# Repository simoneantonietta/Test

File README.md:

# Test
Test repository

The repository contains PCB and uC project files

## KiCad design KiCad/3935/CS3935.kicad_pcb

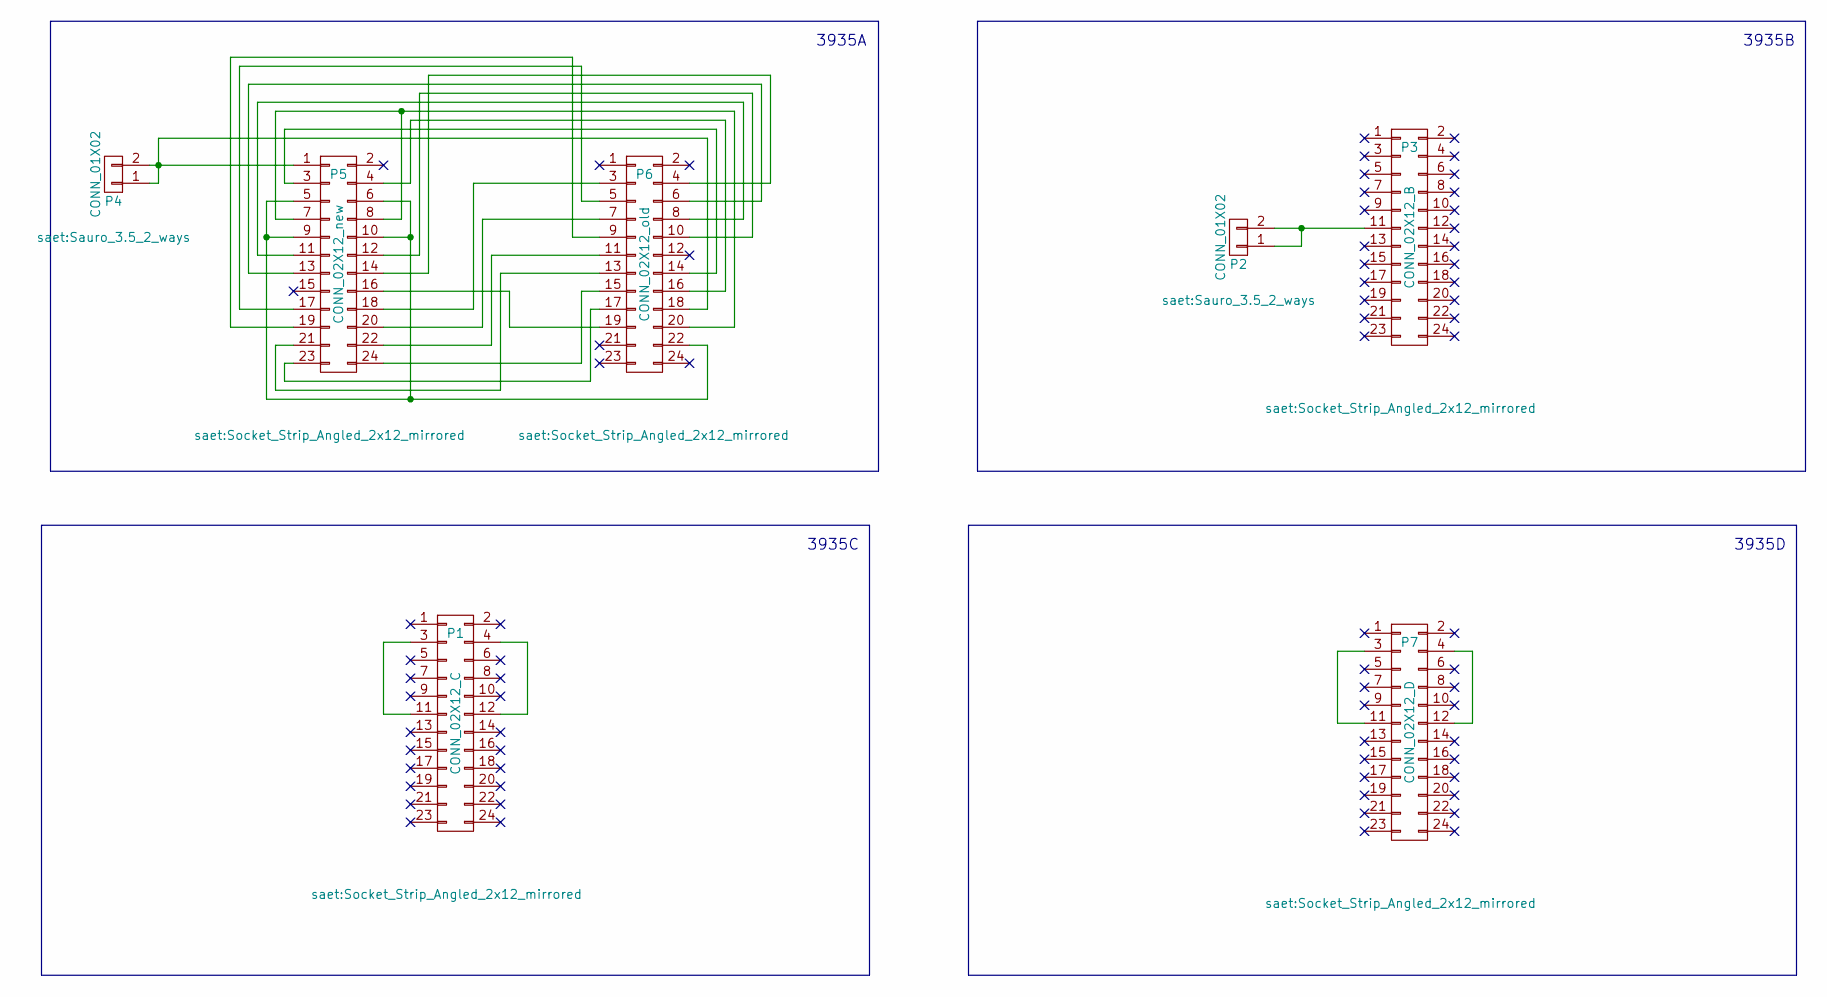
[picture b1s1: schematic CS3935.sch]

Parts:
P1: CONN_02X12_C; Socket_Strip_Angled_2x12_mirrored
P2, P4: CONN_01X02; Sauro_3.5_2_ways
P3: CONN_02X12_B; Socket_Strip_Angled_2x12_mirrored
P5: CONN_02X12_new; Socket_Strip_Angled_2x12_mirrored
P6: CONN_02X12_old; Socket_Strip_Angled_2x12_mirrored
P7: CONN_02X12_D; Socket_Strip_Angled_2x12_mirrored

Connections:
unnamed: P1.3, P1.11
unnamed: P1.4, P1.12
unnamed: P2.1, P2.2, P3.11
unnamed: P4.1, P4.2, P5.1, P6.18
unnamed: P5.3, P6.14
unnamed: P5.4, P6.16
unnamed: P5.7, P5.8, P6.20
unnamed: P5.5, P5.6, P5.9, P5.10, P6.22
unnamed: P5.11, P6.8
unnamed: P5.12, P6.10
unnamed: P5.13, P6.6
unnamed: P5.14, P6.4
unnamed: P5.16, P6.19
unnamed: P5.17, P6.5
unnamed: P5.18, P6.3
unnamed: P5.19, P6.9
unnamed: P5.20, P6.7
unnamed: P5.21, P6.13
unnamed: P5.22, P6.11
unnamed: P5.23, P6.17
unnamed: P5.24, P6.15
unnamed: P7.3, P7.11
unnamed: P7.4, P7.12

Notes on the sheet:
3935B
3935A
3935D
3935C

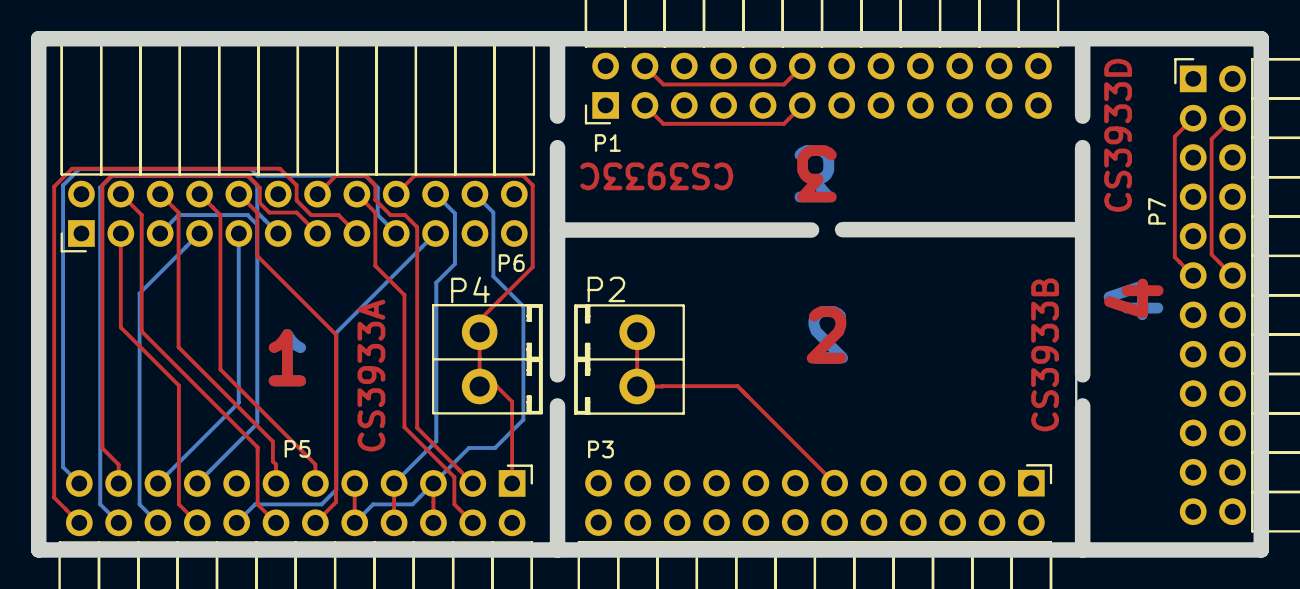
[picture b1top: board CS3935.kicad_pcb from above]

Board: 2 copper layers, 78.9 x 33.0 mm, 7 parts (0 on the bottom side), 23 nets.

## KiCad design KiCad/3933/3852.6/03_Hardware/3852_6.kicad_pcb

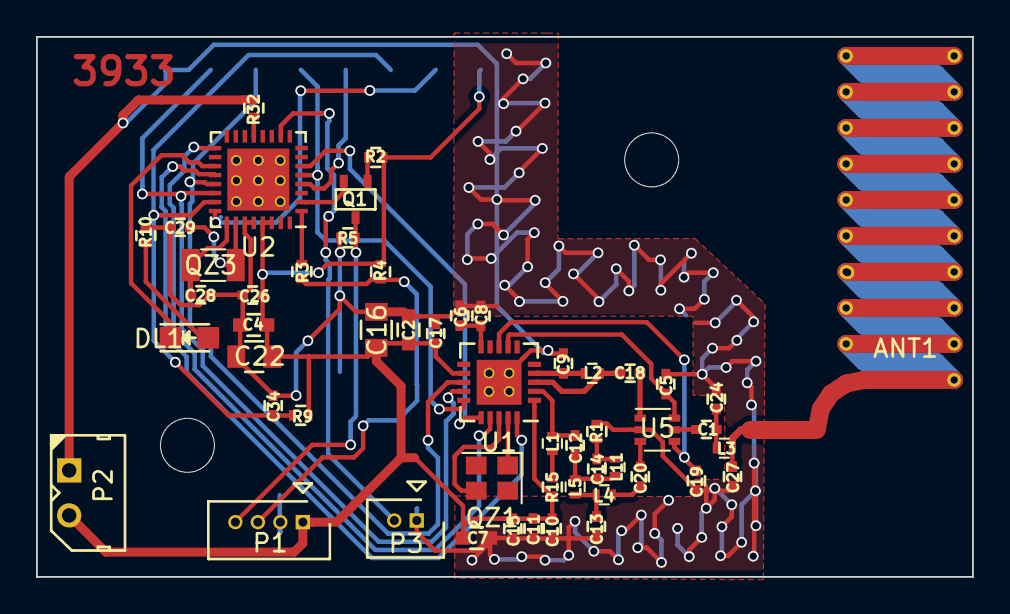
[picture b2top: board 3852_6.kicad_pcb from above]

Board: 2 copper layers, 52.0 x 30.0 mm, 55 parts (0 on the bottom side), 40 nets.

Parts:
ANT1: Antenna PCB; antenna_pcb_complete_reversed
C1, C20: 68p; C_0402
C2: 4u7; C_0603
C4: 10u; C_0603
C5, C19: 1p; C_0402
C6: 1u; C_0402
C7: 2u2; C_0603
C8, C15, C17, C26: 100n; C_0402
C9: 3p9; C_0402
C10: 33p; C_0402
C11: 100p; C_0402
C12: 39p; C_0402
C13: 3p3; C_0402
C14: 6p; C_0402
C16, C22: 47u/50V; C_0805
C18: 6p8; C_0402
C24, C27: 4p7; C_0402
C28, C29: 56p; C_0402
C34: 2n2; C_0402
CN3: STRIP Prog.; strip_pad_x8
DL1: LEDR-LHN974; LED_0805
HOLE_3mm, HOLE_3mm#2: VAL**; HOLE_3mm
L1: 120n; L_0402
L2: 11n; L_0402
L3: 9n; L_0402
L4, L5: 15n; L_0402
L11: 5n6; L_0402
P1: SERIAL CONNECTOR; Connector_Molex_PicoBlade_53047-0410
P2: JBAT; molex_22-03-5025
P3: TAMPER CONNECTOR; Connector_Molex_PicoBlade_53047-0210
Q1: Q_NMOS_DGS; SC-70
QZ1: 30MHz; Crystal_SMD_2520-4pin_2.5x2.0mm
QZ3: 32KHz; Crystal_SMD_3215-2pin_3.2x1.5mm
R1: 50; R_0402
R2, R3: 1k; R_0402
R4: 2,2M; R_0402
R5, R15, R32: 0; R_0402
R9: 47K; R_0402
R10: 470; R_0402
U1: SI4432B; QFN-20-1EP_4x4mm_Pitch0.5mm_with_back_holes
U2: MSP430G2433IRHN32; QFN-32-1EP_5x5mm_Pitch0.5mm_with_back_holes
U5: UPG2214TB; SOT-363_SC-70-6

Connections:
/RX: R3.1, U2.1
/TX: Q1.2, U2.2
/White: P1.3, R3.2, R4.2
/Yellow: P1.4, Q1.3, R5.1
CLK: CN3.4, U1.15, U2.5
CS: U1.16, U2.6
GND: C2.2, C4.2, C5.2, C6.2, C7.2, C8.2, C9.2, C10.2, C11.2, C13.2, C15.2, C16.2, C17.2, C19.2, C22.2, C24.2, C26.2, C27.2, C28.1, C29.1, C34.2, CN3.1, P1.2, P2.1, P3.1, R1.2, R5.2, R10.1, R32.2, U1.21, U2.27, U2.28, U5.2
IRQ: U1.17, U2.17
unnamed: ANT1.1, C27.1, L3.1
unnamed: C1.1, C24.1, L3.2
unnamed: C1.2, U5.5
unnamed: C5.1, U1.7, U5.6
unnamed: C6.1, C8.1, U1.10
unnamed: C9.1, L2.2, U1.4
unnamed: C12.1, C14.1, L5.2, L11.1
unnamed: C12.2, L1.1, U1.2
unnamed: C13.1, L4.2, L5.1
unnamed: C14.2, L11.2, R1.1
unnamed: C18.1, U5.1
unnamed: C18.2, L2.1, U1.3
unnamed: C19.1, U1.8, U5.4
unnamed: C20.1, L4.1
unnamed: C20.2, U5.3
unnamed: C28.2, QZ3.2, U2.25
unnamed: C29.2, QZ3.1, U2.26
unnamed: C34.1, CN3.6, R9.2, U2.23
unnamed: CN3.5, U2.4
unnamed: CN3.7, U2.24
unnamed: DL1.1, U2.19
unnamed: DL1.2, R10.2
unnamed: L1.2, R15.2
unnamed: P3.2, U2.10
unnamed: Q1.1, R2.1
unnamed: QZ1.1, U1.19
unnamed: QZ1.3, U1.18
unnamed: R32.1, U2.13
PD: U1.20, U2.20
SI: CN3.2, U1.14, U2.22
SO: CN3.3, U1.13, U2.21
VCC: C2.1, C4.1, C7.1, C10.1, C11.1, C15.1, C16.1, C17.1, C22.1, C26.1, CN3.8, P1.1, P2.2, R2.2, R4.1, R9.1, R15.1, U1.1, U1.12, U2.29, U2.30

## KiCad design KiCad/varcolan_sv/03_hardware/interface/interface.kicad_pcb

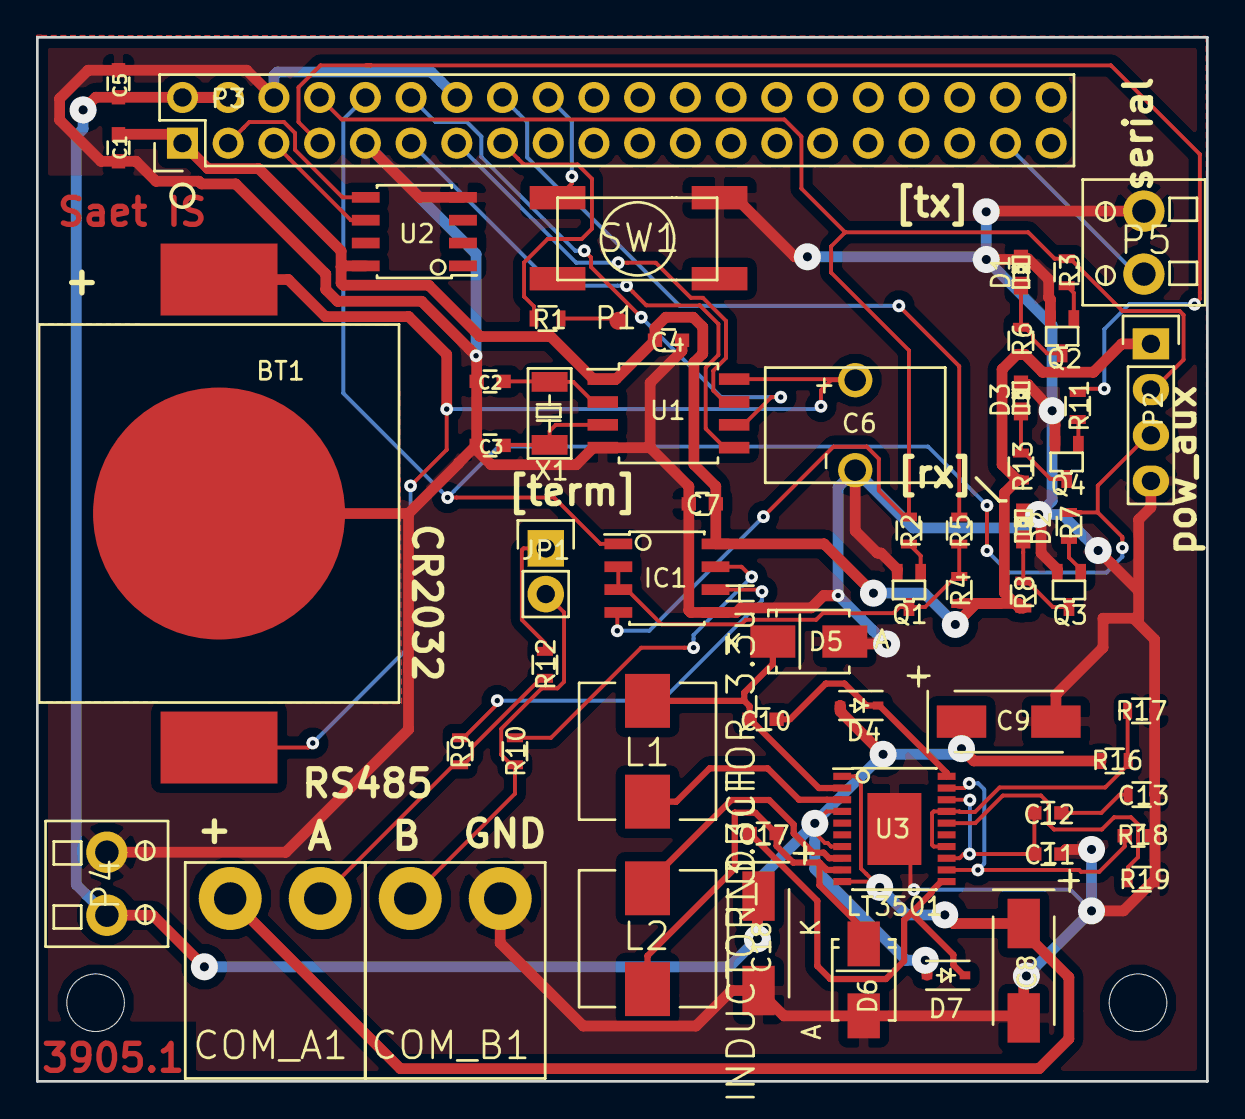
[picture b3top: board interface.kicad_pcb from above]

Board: 2 copper layers, 65.0 x 58.0 mm, 62 parts (0 on the bottom side), 44 nets.

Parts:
BT1: Battery; BatteryHolderCR2032
C1, C4, C5, C7, C13: 100n; C_0603
C2, C3: 12p; C_0603
C6: 0.33F; SUPER_CAP
C8, C9, C18: 22u/20V; TantalC_SizeC_EIA-6032_Wave
C10: 470n; C_0603
C11: 10p; C_0603
C12: 470p; C_0603
C17: 0.47u; C_0603
COM_A1: WURTH_90; Wurth_90_deg_2ways
COM_B1: WURTH_90; Wurth_90_deg_2ways
D1, D2, D3: LED_R_0603; LED-0603_handSoldering
D4, D7: PMEG4005AEA; SOD-323
D5, D6: B360A; SMA_Standard
HL1, HL2: Hole; HOLE_3.2
IC1: SN65HVD11D; SOIC-8
JP1: JUMPER; Pin_Header_Straight_1x02
L1, L2: INDUCTOR_3.3uH; IND_7.5x7.5
P1: TP; Test_point
P2: CONN_01X04; Pin_Header_Straight_1x04
P3: CONN_02X20; Pin_Header_Straight_2x20
P4: CONN_01X02; Adimpex_3.5_2_ways
P5: TAMPER CONN; Adimpex_3.5_2_ways
Q1, Q2, Q3, Q4: RJU003N; SOT-323_inv
R1, R5: 0; R_0603
R2, R4: 10k; R_0603
R3, R7, R11: 1k; R_0603
R6, R8, R13: 510; R_0603
R9, R10: 10; R_0603
R12: 120; R_0603
R16, R18: 40.2k; R_0603
R17: 7.68k; R_0603
R19: 30.1k; R_0603
SW1: Switch; Switch_DTSM_6_Series
U1: DS1302S; SOIJ-8_5.3x5.3mm_Pitch1.27mm
U2: ATECC508a; SOIC-8
U3: LT3501; SSOP-20_TP_4.4x6.5mm_Pitch0.65mm
X1: JXS_32k; JXS_3.2mm_1.5mm

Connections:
+3.3V: C1.1, C4.1, C7.1, IC1.8, P2.1, P3.1, R4.1, R6.1, R8.1, R13.1, U1.1, U2.8
+5V: C5.1, C9.1, C18.1, D4.1, D7.1, P3.2, P3.4, P4.1, R16.1, U3.4, U3.7
+13.8V: C8.1, COM_A1.2, U3.1, U3.10
/Power supply/_pwrA1: C10.2, D5.2, L1.2, U3.2
/Power supply/_pwrA2: L1.1, U3.3
/Power supply/_pwrA3: C17.2, D6.2, L2.1, U3.9
/Power supply/_pwrA4: L2.2, U3.8
/Power supply/_pwrA5: C10.1, D4.2, U3.20
/Power supply/_pwrA6: C17.1, D7.2, U3.11
/dir: P3.16, R5.1
/led: P3.7, R11.2
/rxd: IC1.1, P2.3, P3.10, R7.2
/scl: P3.5, U2.6
/sda: P3.3, U2.5
/spi_ce: P3.11, U1.5
/spi_io: P3.12, U1.6
/spi_sck: P3.13, U1.7
/txd: IC1.4, P2.2, P3.8, R2.2, R3.2
GND: BT1.2, C1.2, C2.2, C3.2, C4.2, C5.2, C6.2, C7.2, C8.2, C9.2, C11.2, C13.2, C18.2, COM_B1.1, D1.2, D2.2, D3.2, D5.1, D6.1, IC1.5, P2.4, P3.6, P3.9, P3.14, P4.2, P5.1, Q1.1, Q2.1, Q3.1, Q4.1, R17.2, R18.2, R19.1, SW1.2, U1.4, U2.4, U3.21
unnamed: BT1.1, C6.1, U1.8
unnamed: C2.1, U1.2, X1.1
unnamed: C3.1, U1.3, X1.2
unnamed: C11.1, C12.1, U3.13, U3.18
unnamed: C12.2, R18.1
unnamed: C13.1, U3.12, U3.19
unnamed: COM_A1.1, R9.1, R12.1
unnamed: COM_B1.2, JP1.2, R10.1
unnamed: D1.1, Q2.3, R6.2
unnamed: D2.1, Q3.3, R8.2
unnamed: D3.1, Q4.3, R13.2
unnamed: IC1.2, IC1.3, Q1.3, R4.2, R5.2
unnamed: IC1.6, R9.2
unnamed: IC1.7, R10.2
unnamed: JP1.1, R12.2
unnamed: P1.1, R1.2
unnamed: P3.15, R1.1
unnamed: P3.18, SW1.1
unnamed: P3.37, P5.2
unnamed: Q1.2, R2.1
unnamed: Q2.2, R3.1
unnamed: Q3.2, R7.1
unnamed: Q4.2, R11.1
unnamed: R16.2, R17.1, U3.14, U3.17
unnamed: R19.2, U3.16

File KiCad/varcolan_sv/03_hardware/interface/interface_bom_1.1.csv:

References,Value,Footprint,Quantity Per PCB,NOT_MOUNT,Saet_code
BT1,Battery,BatteryHolderCR2032,1,X,
C6,0.33F,SUPER_CAP,1,,CV1476
C1 C4 C5 C7 C13,100n,C_0603,5,,
C11,10p,C_0603,1,,
C2 C3,12p,C_0603,2,,
C8 C9 C18,22u/20V,TantalC_SizeC_EIA-6032_Wave,3,,CV0226
C10 C17,470n,C_0603,2,,
C12,470p,C_0603,1,,
COM_A1 COM_B1,WURTH_90,Wurth_90_deg_2ways,2,,WK2320
D5 D6,B360A,SMA_Standard,2,,DSB360A
D1 D2 D3,LED_R_0603,LED-0603_handSoldering,3,,LE7010
D4 D7,PMEG4005AEA,SOD-323,2,,DSG4005
HL1 HL2,Hole,HOLE_3.2,2,,
IC1,SN65HVD11D,SOIC-8,1,,IL1138
JP1,JUMPER,Pin_Header_Straight_1x02,1,,
L1 L2,INDUCTOR_3.3uH,IND_7.5x7.5,2,,TB3020
P4,CONN_01X02,Adimpex_3.5_2_ways,1,X,
P2,CONN_01X04,Pin_Header_Straight_1x04,1,X,
P3,CONN_02X20,Pin_Header_Straight_2x20,1,,
P5,TAMPER CONN,Adimpex_3.5_2_ways,1,,
Q1 Q2 Q3 Q4,RJU003N,SOT-323_inv,4,,QT3134
R1 R5,0,R_0603,2,X,
R9 R10,10,R_0603,2,,
R2 R4,10k,R_0603,2,,
R12,120,R_0603,1,,
R3 R7 R11,1k,R_0603,3,,
R19,30.1k,R_0603,1,,
R16 R18,40.2k,R_0603,2,,
R6 R8 R13,510,R_0603,3,,
R17,7.68k,R_0603,1,,
SW1,Switch,Switch_DTSM_6_Series,1,,
U2,ATECC508a,SOIC-8,1,,
U1,DS1302S,SOIJ-8_5.3x5.3mm_Pitch1.27mm,1,,IT001
U3,LT3501,SSOP-20_TP_4.4x6.5mm_Pitch0.65mm,1,,IL1186
X1,JXS_32k,JXS_3.2mm_1.5mm,1,,YQ1323B

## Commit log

2018-10-24 Readme ended
2018-10-24 Optex and Varcolan projects
2018-10-24 project files loaded
2018-10-24 Varcolan project added
2018-10-24 Optex project added
2018-10-24 readme updates
2018-10-31 Upgrade: PCB topo changes
2018-10-31 directory changes
2018-11-15 Update on Micro tests
2018-12-27 Kicad and firmware updates
2018-12-27 Library update
2018-12-27 Kicad libraries update
2019-01-02 Aggiornamenti su modulo SPI (sw->hw) e vari sui circuiti
2019-01-08 Inserimento buchi sul CS per alloggiare supporti in gomma
2019-01-31 Versione firmware Optex funzionante con Contatto semplice (no tapparella) e Optex Hardware aggiornamento con file rinominati in CS3933 CS3934 CS3935
2019-01-31 CS3934 CS3935
2019-08-02 Aggiunti vari footprint
2019-08-08 Aggiunta antenna 13MHz bottom
2019-08-09 Aggiunta antenna 13MHz asimmetrica
2019-10-31 aggiunto footprint modulo BLE
2019-10-31 Inserito componente BLE
2019-10-31 Aggiornati file per libreria saet
2019-11-22 Aggiunto TPS62125
2019-11-22 Aggiunto footprint induttore LQH32
2019-11-22 Aggiunto SOD-128
2019-11-25 Aggiunto SOT-313-2 per lpc1115
2019-11-25 Aggiunto connettore batteria
2019-11-25 Aggiunto footprint filtro EMI da 2mm
2019-11-26 Aggiunto quarzo con pin diagonali
2019-12-06 Aggiunto componente e footprint del PMEG45A10EPD
2019-12-23 Aggiunto fusibile 2920
2019-12-23 Aggiunto diodo standard (zener)
2020-01-07 Aggiunto SOIC-8 con massa sotto al componente
2020-01-07 Aggiornato LTC2862
2020-01-31 Corretto dip switch 4
2020-02-06 Aggiornato TPS62125
2020-02-28 Aggiornati diversi footprint, come il connetore a vaschetta, e aggiunto il footprint goccia di stagno
2020-02-28 Aggiunto simbolo 13.8V2, corretto simbolo alimentatore switching
2020-04-10 Aggiunto simbolo Logo Saet
2020-04-24 Aggiunto componente e footprint CPU STM32MP151AAC3
2020-04-27 Aggiornato pinout STM32MP151AAC3
2020-04-28 Aggiornato simbolo STM32MP151AAC
2020-05-04 Aggiunti pin oscillatore 32kHz
2020-05-04 Aggiornati pin di alimentazione come power_input
2020-07-07 Aggiunti PMIC e MAX per alimentazione Cartesio
2020-07-23 Aggiunti componenti LAN per progetto Cartesio
2020-07-27 Aggiunto componente led holder contenente uno stack di 2 led
2020-07-28 Aggiunti induttori e ptc
2020-08-03 Corretto componente CPU STM32MP151 unit E
2020-08-03 Aggiunti GPIO per CPU STM32MP151
2020-08-03 Aggiunto componente NAND flash
2020-08-03 Aggiunto modello 3D bga 63
2020-08-04 aggiunto footprint micro SD holder
2020-08-04 Inserito simbolo micro sd holder
2020-08-05 Corretto footprint cpu STM32MP
2020-08-05 Aggiornato componente pmic con più pad sotto al comp onente per predisposizione a un numero maggiore di via per dissipazione termica
2020-08-10 Aggiornato componente STM32MP151AAC3-unitB
2020-08-10 Corretto simbolo NAND Flash
2020-08-12 Aggiornato footprint PMIC
2020-12-04 Aggiunto componente MT41K512M16 - DDR3
2020-12-04 Miglioramenti simboli componenti Cartesio: MCU e DDR
2021-01-18 Aggiunto footprint FRAM FM25L256
2021-01-18 Aggiunto componente crypto chip
2021-01-19 Aggiunta pin U3 e U4 a simbolo STM32MP151AAC3
2021-01-19 Separati segnali DNU nel simbolo STM32MP151AAC3
2021-01-20 Aggiunto componente di protezione ESD su USB
